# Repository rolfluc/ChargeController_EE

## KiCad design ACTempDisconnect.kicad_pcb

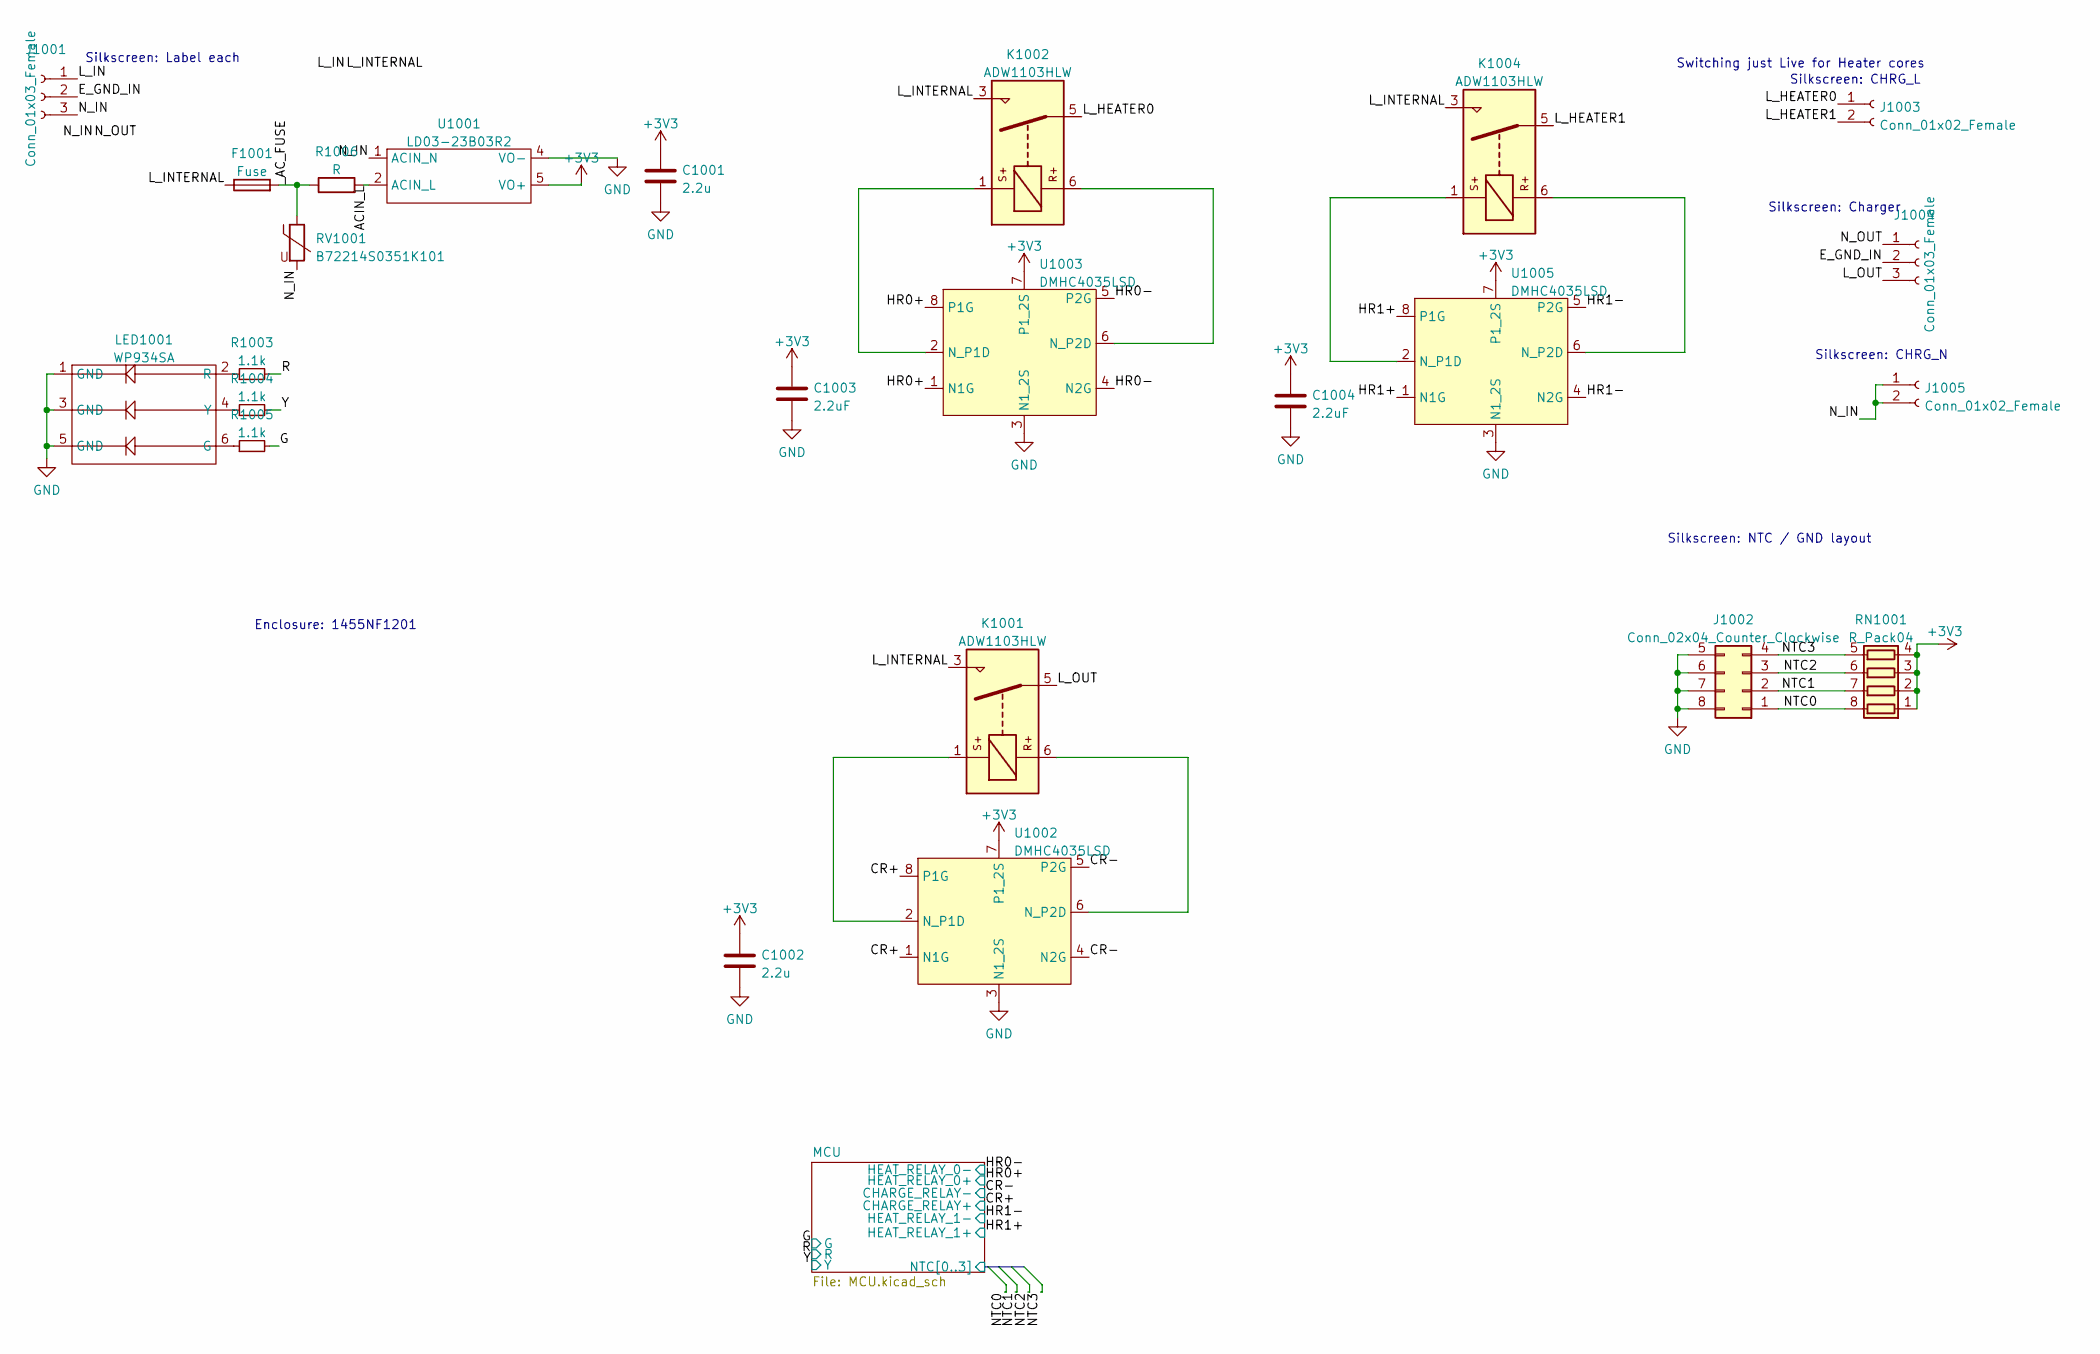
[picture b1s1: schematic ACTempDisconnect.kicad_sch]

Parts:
C1001: 2.2u; C_0603_1608Metric_Pad1.08x0.95mm_HandSolder
C1002: 2.2u; C_0805_2012Metric_Pad1.18x1.45mm_HandSolder
C1003, C1004: 2.2uF; C_0805_2012Metric_Pad1.18x1.45mm_HandSolder
F1001: Fuse; 0680L2000-05; MPN 0680L2000-05
J1001: Conn_01x03_Female; OSTT7030150
J1002: Conn_02x04_Counter_Clockwise; 736-104
J1003, J1005: Conn_01x02_Female; OSTT7020150; MPN OSTT7020150
J1004: Conn_01x03_Female; OSTT7030150; MPN OSTT7030150
K1001, K1002, K1004: ADW1103HLW; Relay_1P1T_NO_10x24x18.8mm_Panasonic_ADW11xxxxW_THT
LED1001: WP934SA; WP934SA_LILYLGD
R1003, R1004, R1005: 1.1k; R_0402_1005Metric_Pad0.72x0.64mm_HandSolder
R1006: R; R_Axial_DIN0204_L3.6mm_D1.6mm_P5.08mm_Horizontal
RN1001: R_Pack04; R_Array_Convex_4x1206; MPN CAT16-102J4LF
RV1001: B72214S0351K101; R_Axial_DIN0614_L14.3mm_D5.7mm_P15.24mm_Horizontal
U1001: LD03-23B03R2
U1002, U1003, U1005: DMHC4035LSD; SOIC-8_3.9x4.9mm_P1.27mm

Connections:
+3V3: C1001.1, C1002.1, C1003.1, C1004.1, RN1001.1 (R1.1), RN1001.2 (R2.1), RN1001.3 (R3.1), RN1001.4 (R4.1), U1001.5 (VO+), U1002.7 (P1_2S), U1003.7 (P1_2S), U1005.7 (P1_2S); also elsewhere on the board
/ACIN_L: R1006.2, U1001.2 (ACIN_L)
/CR+: U1002.1 (N1G), U1002.8 (P1G); also elsewhere on the board
/CR-: U1002.4 (N2G), U1002.5 (P2G); also elsewhere on the board
/E_GND_IN: J1001.2, J1004.2
/G: R1005.2; also elsewhere on the board
/HR0+: U1003.1 (N1G), U1003.8 (P1G); also elsewhere on the board
/HR0-: U1003.4 (N2G), U1003.5 (P2G); also elsewhere on the board
/HR1+: U1005.1 (N1G), U1005.8 (P1G); also elsewhere on the board
/HR1-: U1005.4 (N2G), U1005.5 (P2G); also elsewhere on the board
/L_HEATER0: J1003.1, K1002.5
/L_HEATER1: J1003.2, K1004.5
/L_IN: F1001.1, J1001.1, K1001.3, K1002.3, K1004.3
/L_OUT: J1004.3, K1001.5
/MCU/NTC0: J1002.1, RN1001.8 (R1.2); also elsewhere on the board
/MCU/NTC1: J1002.2, RN1001.7 (R2.2); also elsewhere on the board
/MCU/NTC2: J1002.3, RN1001.6 (R3.2); also elsewhere on the board
/MCU/NTC3: J1002.4, RN1001.5 (R4.2); also elsewhere on the board
/N_IN: J1001.3, J1004.1, J1005.1, J1005.2, RV1001.2, U1001.1 (ACIN_N)
/R: R1003.2; also elsewhere on the board
/Y: R1004.2; also elsewhere on the board
/_AC_FUSE: F1001.2, R1006.1, RV1001.1
GND: C1001.2, C1002.2, C1003.2, C1004.2, J1002.5, J1002.6, J1002.7, J1002.8, LED1001.1 (GND), LED1001.3 (GND), LED1001.5 (GND), U1001.4 (VO-), U1002.3 (N1_2S), U1003.3 (N1_2S), U1005.3 (N1_2S); also elsewhere on the board
unnamed: K1001.1, U1002.2 (N_P1D)
unnamed: K1001.6, U1002.6 (N_P2D)
unnamed: K1002.1, U1003.2 (N_P1D)
unnamed: K1002.6, U1003.6 (N_P2D)
unnamed: K1004.1, U1005.2 (N_P1D)
unnamed: K1004.6, U1005.6 (N_P2D)
unnamed: LED1001.2 (R), R1003.1
unnamed: LED1001.4 (Y), R1004.1
unnamed: LED1001.6 (G), R1005.1

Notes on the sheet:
Switching just Live for Heater cores
Silkscreen: Label each
Silkscreen: Charger
Silkscreen: NTC / GND layout
Silkscreen: CHRG_L
Silkscreen: CHRG_N
Enclosure: 1455NF1201

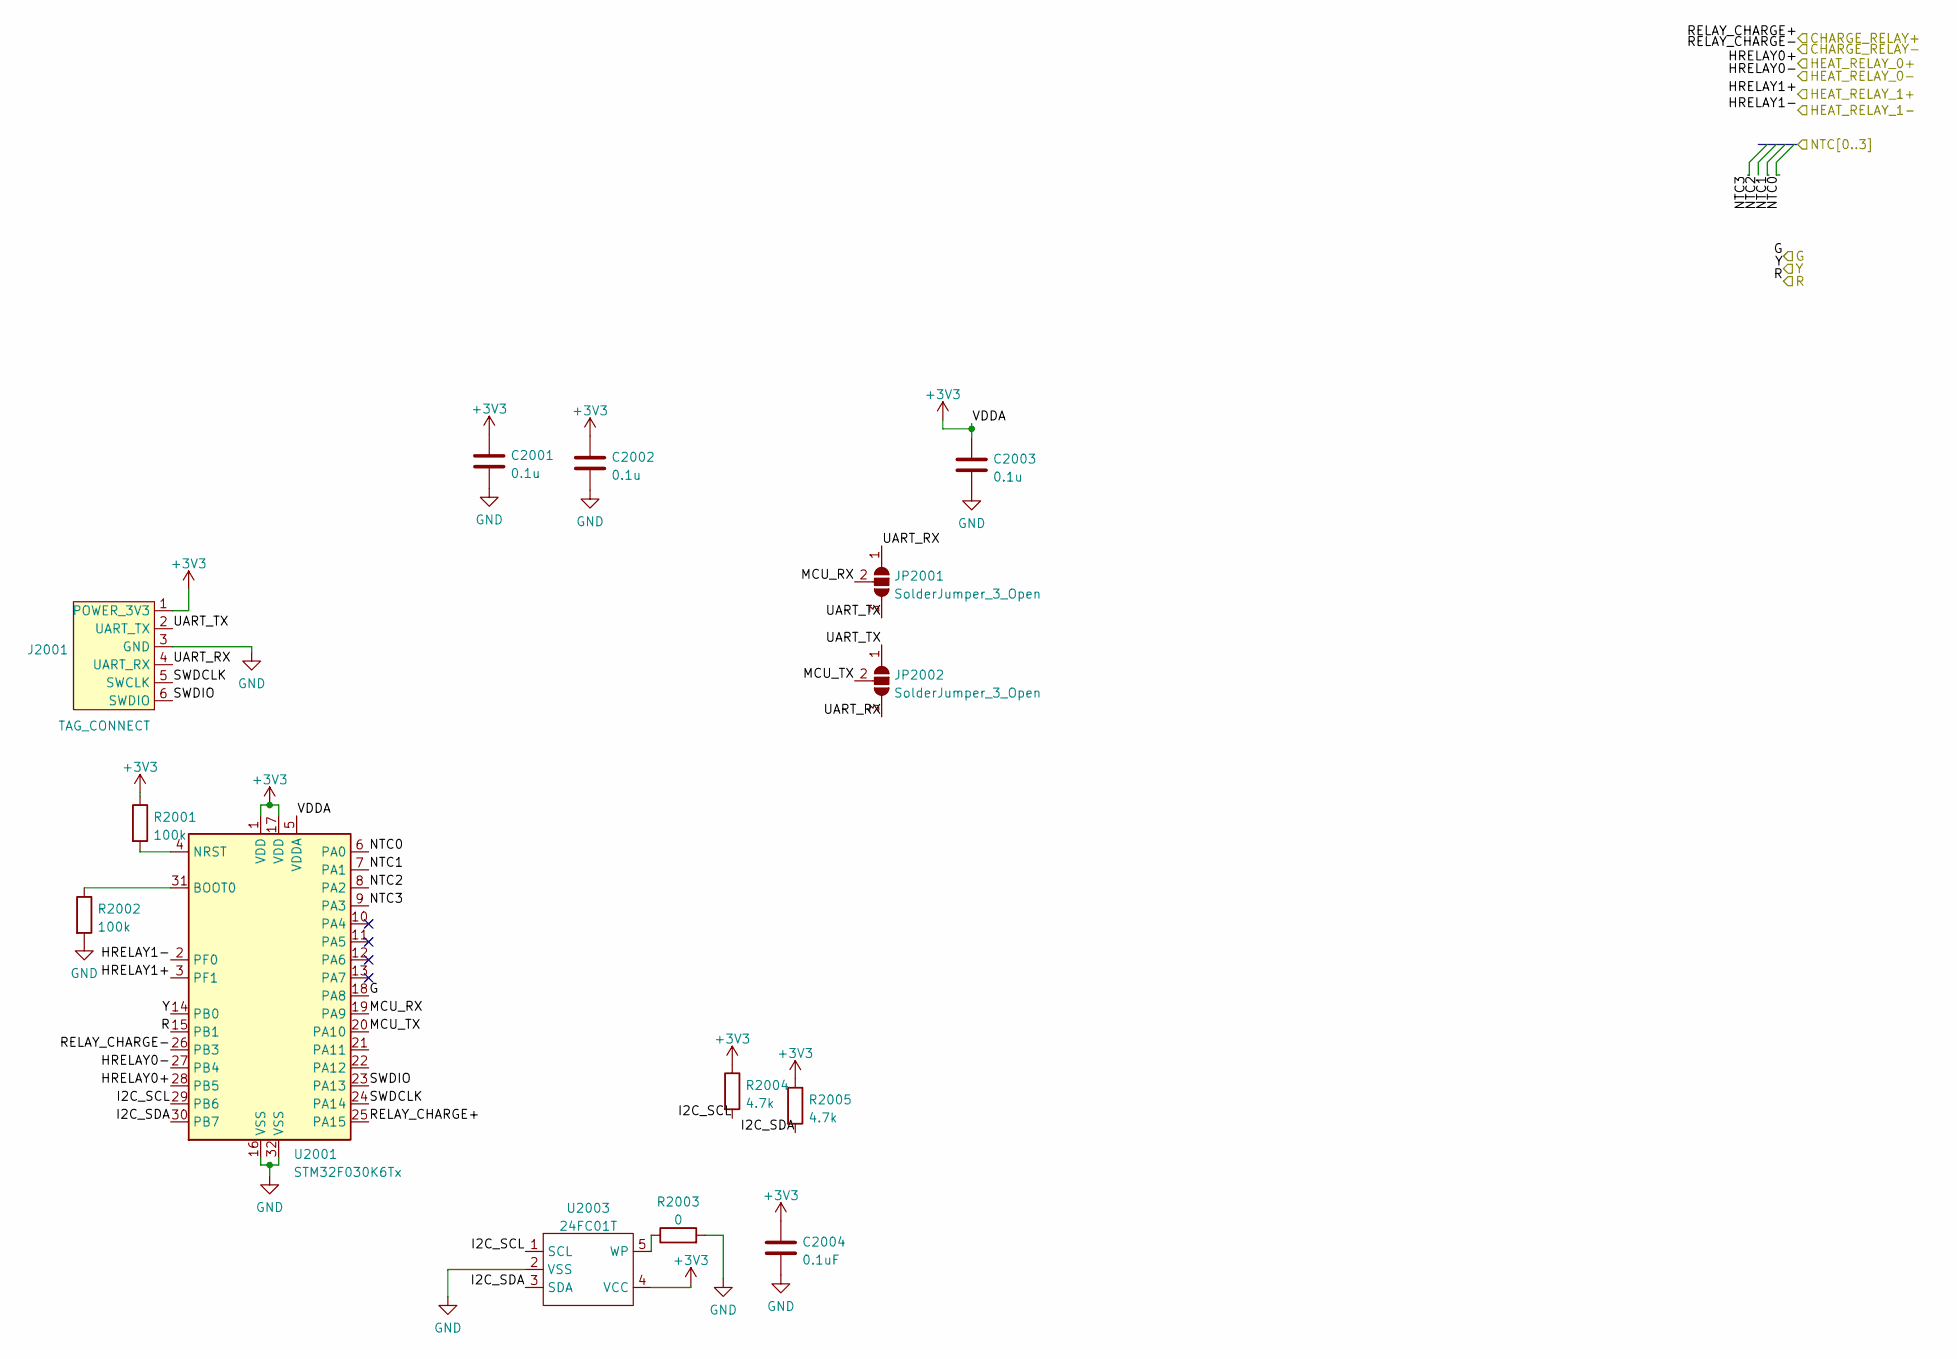
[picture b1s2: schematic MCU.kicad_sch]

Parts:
C2001, C2002, C2003: 0.1u; C_0402_1005Metric_Pad0.74x0.62mm_HandSolder
C2004: 0.1uF; C_0603_1608Metric_Pad1.08x0.95mm_HandSolder
J2001: TAG_CONNECT; Tag-Connect_TC2030-IDC-FP_2x03_P1.27mm_Vertical
JP2001, JP2002: SolderJumper_3_Open; SolderJumper-3_P1.3mm_Open_Pad1.0x1.5mm
R2001, R2002: 100k; R_0402_1005Metric_Pad0.72x0.64mm_HandSolder
R2003: 0; R_0402_1005Metric_Pad0.72x0.64mm_HandSolder
R2004, R2005: 4.7k; R_0402_1005Metric_Pad0.72x0.64mm_HandSolder
U2001: STM32F030K6Tx; LQFP-32_7x7mm_P0.8mm
U2003: 24FC01T; SOT-23-5_HandSoldering

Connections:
+3V3: C2001.1, C2002.1, C2003.1, C2004.1, J2001.1 (POWER_3V3), R2001.1, R2004.1, R2005.1, U2001.1 (VDD), U2001.5 (VDDA), U2001.17 (VDD), U2003.4 (VCC); also elsewhere on the board
/CR+: U2001.25 (PA15); also elsewhere on the board
/CR-: U2001.26 (PB3); also elsewhere on the board
/G: U2001.18 (PA8); also elsewhere on the board
/HR0+: U2001.28 (PB5); also elsewhere on the board
/HR0-: U2001.27 (PB4); also elsewhere on the board
/HR1+: U2001.3 (PF1); also elsewhere on the board
/HR1-: U2001.2 (PF0); also elsewhere on the board
/MCU/I2C_SCL: R2004.2, U2001.29 (PB6), U2003.1 (SCL)
/MCU/I2C_SDA: R2005.2, U2001.30 (PB7), U2003.3 (SDA)
/MCU/MCU_RX: JP2001.2 (C), U2001.19 (PA9)
/MCU/MCU_TX: JP2002.2 (C), U2001.20 (PA10)
/MCU/NTC0: U2001.6 (PA0); also elsewhere on the board
/MCU/NTC1: U2001.7 (PA1); also elsewhere on the board
/MCU/NTC2: U2001.8 (PA2); also elsewhere on the board
/MCU/NTC3: U2001.9 (PA3); also elsewhere on the board
/MCU/SWDCLK: J2001.5 (SWCLK), U2001.24 (PA14)
/MCU/SWDIO: J2001.6 (SWDIO), U2001.23 (PA13)
/MCU/UART_RX: J2001.4 (UART_RX), JP2001.1 (A), JP2002.3 (B)
/MCU/UART_TX: J2001.2 (UART_TX), JP2001.3 (B), JP2002.1 (A)
/R: U2001.15 (PB1); also elsewhere on the board
/Y: U2001.14 (PB0); also elsewhere on the board
GND: C2001.2, C2002.2, C2003.2, C2004.2, J2001.3 (GND), R2002.2, R2003.2, U2001.16 (VSS), U2001.32 (VSS), U2003.2 (VSS); also elsewhere on the board
unnamed: R2001.2, U2001.4 (NRST)
unnamed: R2002.1, U2001.31 (BOOT0)
unnamed: R2003.1, U2003.5 (WP)

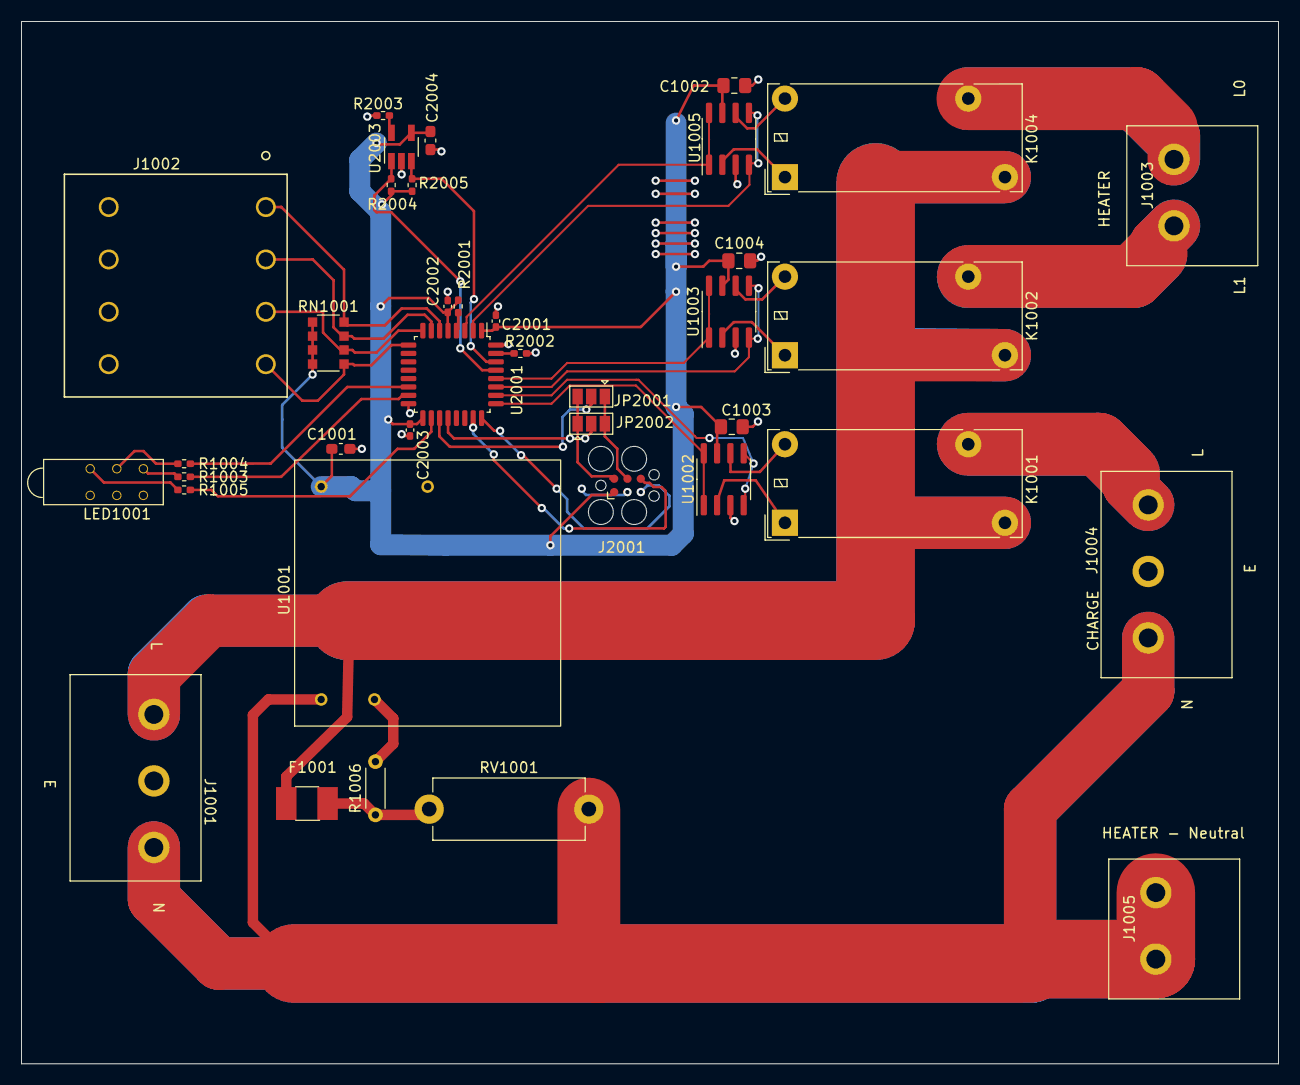
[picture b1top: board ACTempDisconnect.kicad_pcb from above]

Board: 2 copper layers, 120.0 x 99.5 mm, 38 parts (0 on the bottom side), 43 nets.

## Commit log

2023-10-15 First Commit - V1 addition
2023-10-15 Removed Neon from V2
2023-10-20 WIP - Redo of A/C Layout
2023-11-03 Rev 2
    Simplified the layout. Reduced down to 2 layers.
    Added top/bottom traces to split the current.
2023-11-04 8 to 4 NTC
    Reduced down from 8 to 4 NTCs, for cost down and packaging
    considerations.
2023-11-09 New Layout for Battery Charge Controller

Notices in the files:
parts and their libraries:
Copyright 2016 Accelerated Designs. All rights reserved.
